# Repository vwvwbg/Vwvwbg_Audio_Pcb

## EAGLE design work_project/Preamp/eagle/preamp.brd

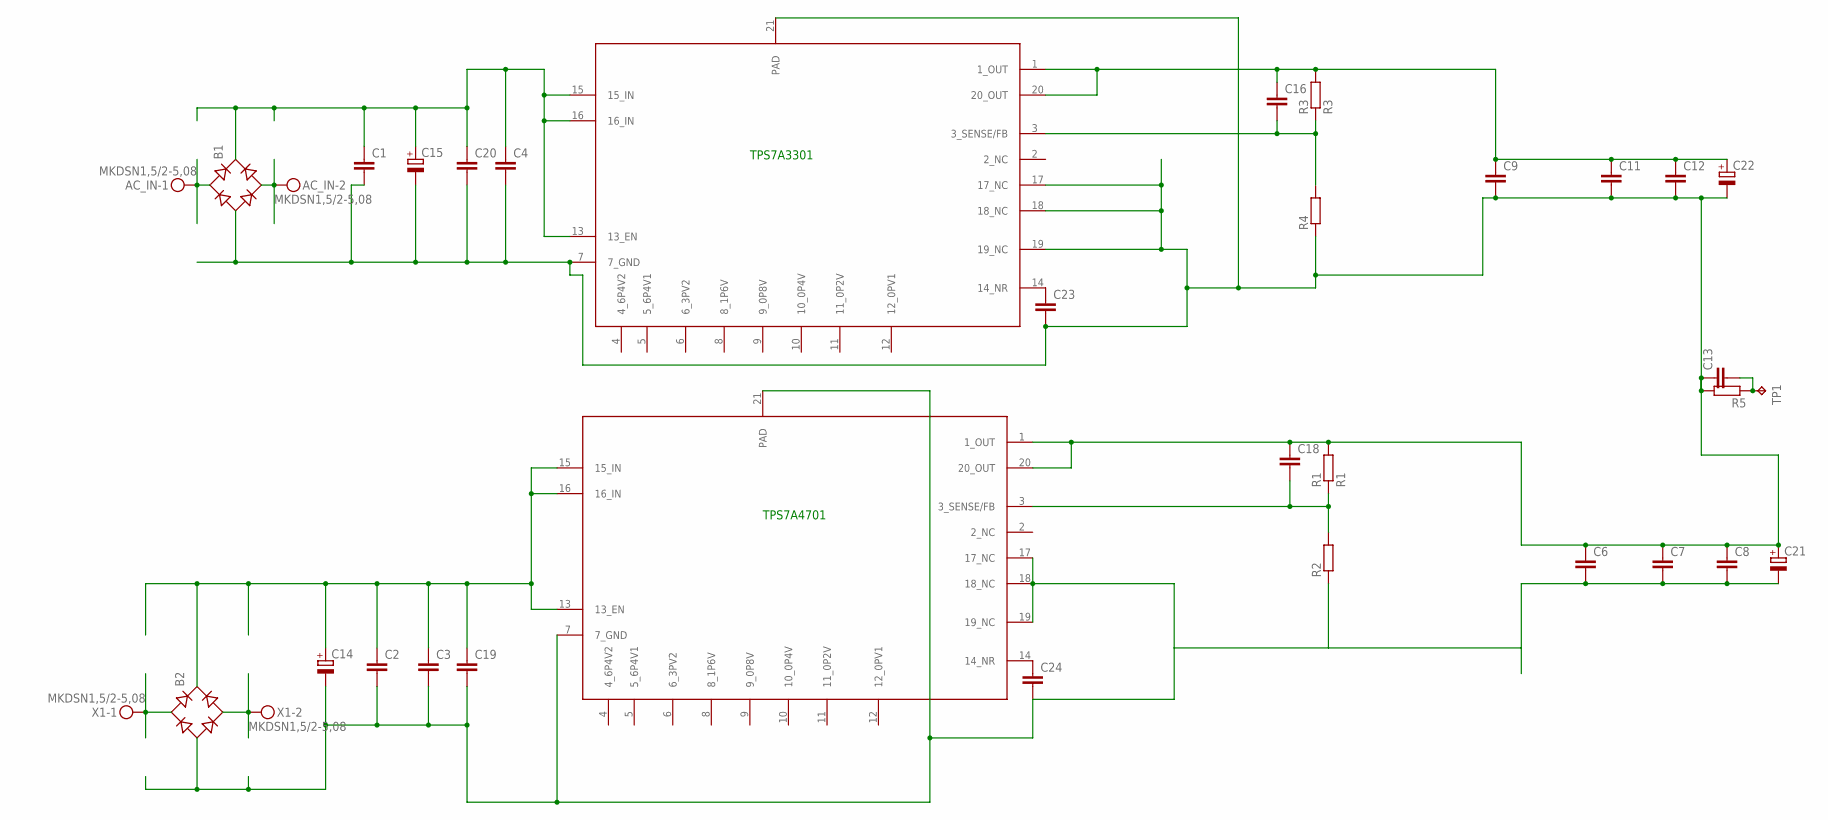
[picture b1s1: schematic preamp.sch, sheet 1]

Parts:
AC_IN: MKDSN1,5/2-5,08
B1, B2: RB1A
C1, C2, C8, C11: C-EUC1210; C1210
C3, C4, C7, C12: C-EUC0805; C0805
C6, C9, C16, C18, C19, C20, C23, C24: C-EUC0603; C0603
C13: C-EU075-042X103; C075-042X103
C14, C15: CPOL-EUE5-13; E5-13
C21, C22: CPOL-EUE3.5-8; E3,5-8
R1: R1; R0805
R2, R4: R-EU_R0805; R0805
R3: R3; R0805
R5: R-EU_0207/12; 0207/12
TP1: TPPAD1-13; P1-13
U$1, U$2: TPS7A4701; QFN65P500X500X100-21N
X1: MKDSN1,5/2-5,08

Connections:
GND: B1.-, C1.2, C4.2, C6.1, C7.1, C8.1, C9.2, C11.2, C12.2, C13.1, C15.-, C18.1, C20.2, C21.+, C22.-, C23.2, R1.2, R4.1, R5.2, U$1.1 (1_OUT), U$1.20 (20_OUT), U$2.7 (7_GND), U$2.17 (17_NC), U$2.18 (18_NC), U$2.19 (19_NC), U$2.21 (PAD); also elsewhere on the board
unnamed: AC_IN.1, B1.AC1
unnamed: B2.+, C2.1, C3.1, C14.+, C19.1, U$1.13 (13_EN), U$1.15 (15_IN), U$1.16 (16_IN)
unnamed: C23.1, U$2.14 (14_NR)
unnamed: C16.2, R3.1, R4.2, U$2.3 (3_SENSE/FB)
unnamed: C24.1, U$1.14 (14_NR)
unnamed: B2.AC2, X1.2
unnamed: B2.AC1, X1.1
unnamed: AC_IN.2, B1.AC2
unnamed: C13.2, R5.1, TP1.TP
unnamed: B1.+, C1.1, C4.1, C15.+, C20.1, U$2.13 (13_EN), U$2.15 (15_IN), U$2.16 (16_IN)
unnamed: C18.2, R1.1, R2.2, U$1.3 (3_SENSE/FB)
V+: C9.1, C11.1, C12.1, C16.1, C22.+, R3.2, U$2.1 (1_OUT), U$2.20 (20_OUT); also elsewhere on the board
V-: B2.-, C2.2, C3.2, C6.2, C7.2, C8.2, C14.-, C19.2, C21.-, C24.2, R2.1, U$1.7 (7_GND), U$1.17 (17_NC), U$1.18 (18_NC), U$1.19 (19_NC), U$1.21 (PAD); also elsewhere on the board

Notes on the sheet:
TPS7A4701
TPS7A3301

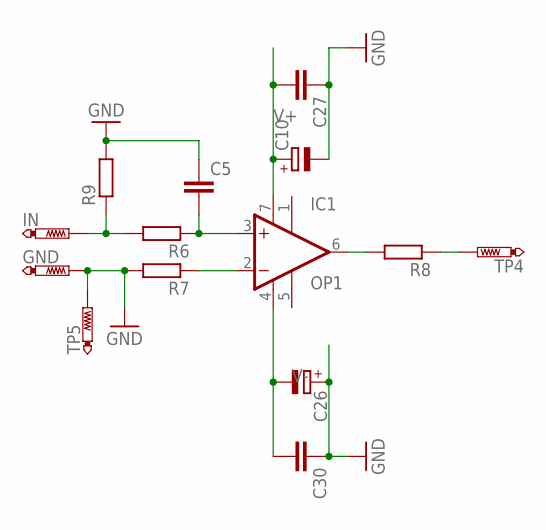
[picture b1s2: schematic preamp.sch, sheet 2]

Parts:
C5: C-EU050-045X075; C050-045X075
C10, C26: CPOL-EUE5-8.5; E5-8,5
C27, C30: C-EU050-030X075; C050-030X075
GND: PTR1PAD1-20; P1-20
IC1: OP1; DIL08
IN: PTR1PAD1-20; P1-20
R6, R7, R8, R9: R-EU_0207/10; 0207/10
TP4, TP5: PTR1PAD1-20; P1-20

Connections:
GND: C5.1, C10.-, C26.+, C27.1, C30.1, GND.TP, R7.2, R9.2, TP5.TP; also elsewhere on the board
unnamed: C5.2, IC1.3 (+IN), R6.1
unnamed: IC1.2 (-IN), R7.1
unnamed: IN.TP, R6.2, R9.1
unnamed: IC1.6 (OUT), R8.2
unnamed: R8.1, TP4.TP
V+: C10.+, C27.2, IC1.7 (V+); also elsewhere on the board
V-: C26.-, C30.2, IC1.4 (V-); also elsewhere on the board

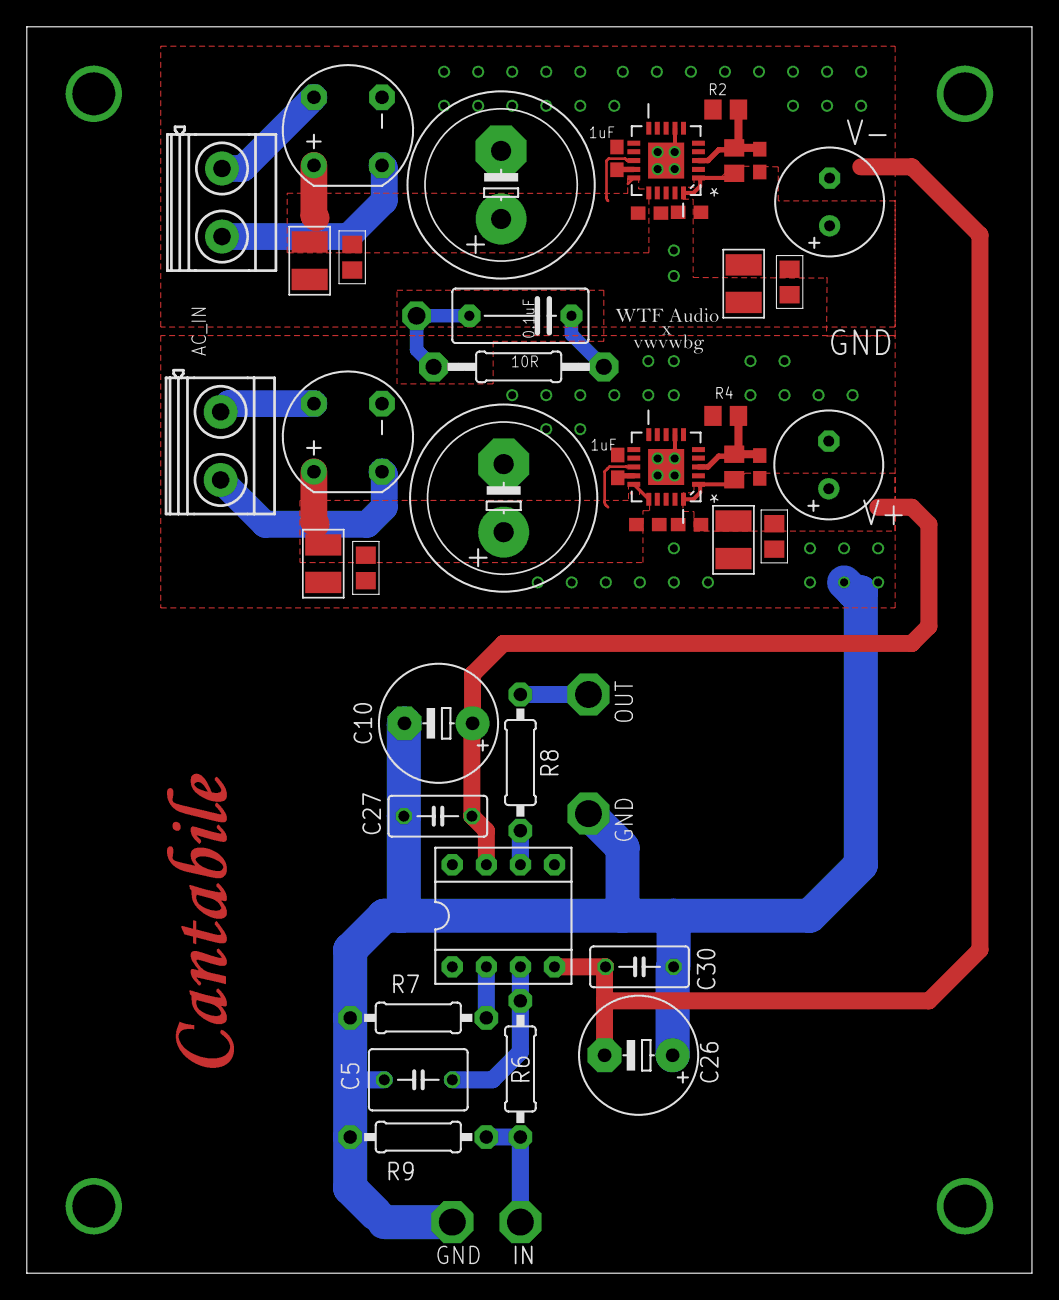
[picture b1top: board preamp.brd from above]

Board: 2 copper layers, 75.0 x 93.0 mm, 47 parts (0 on the bottom side), 19 nets.

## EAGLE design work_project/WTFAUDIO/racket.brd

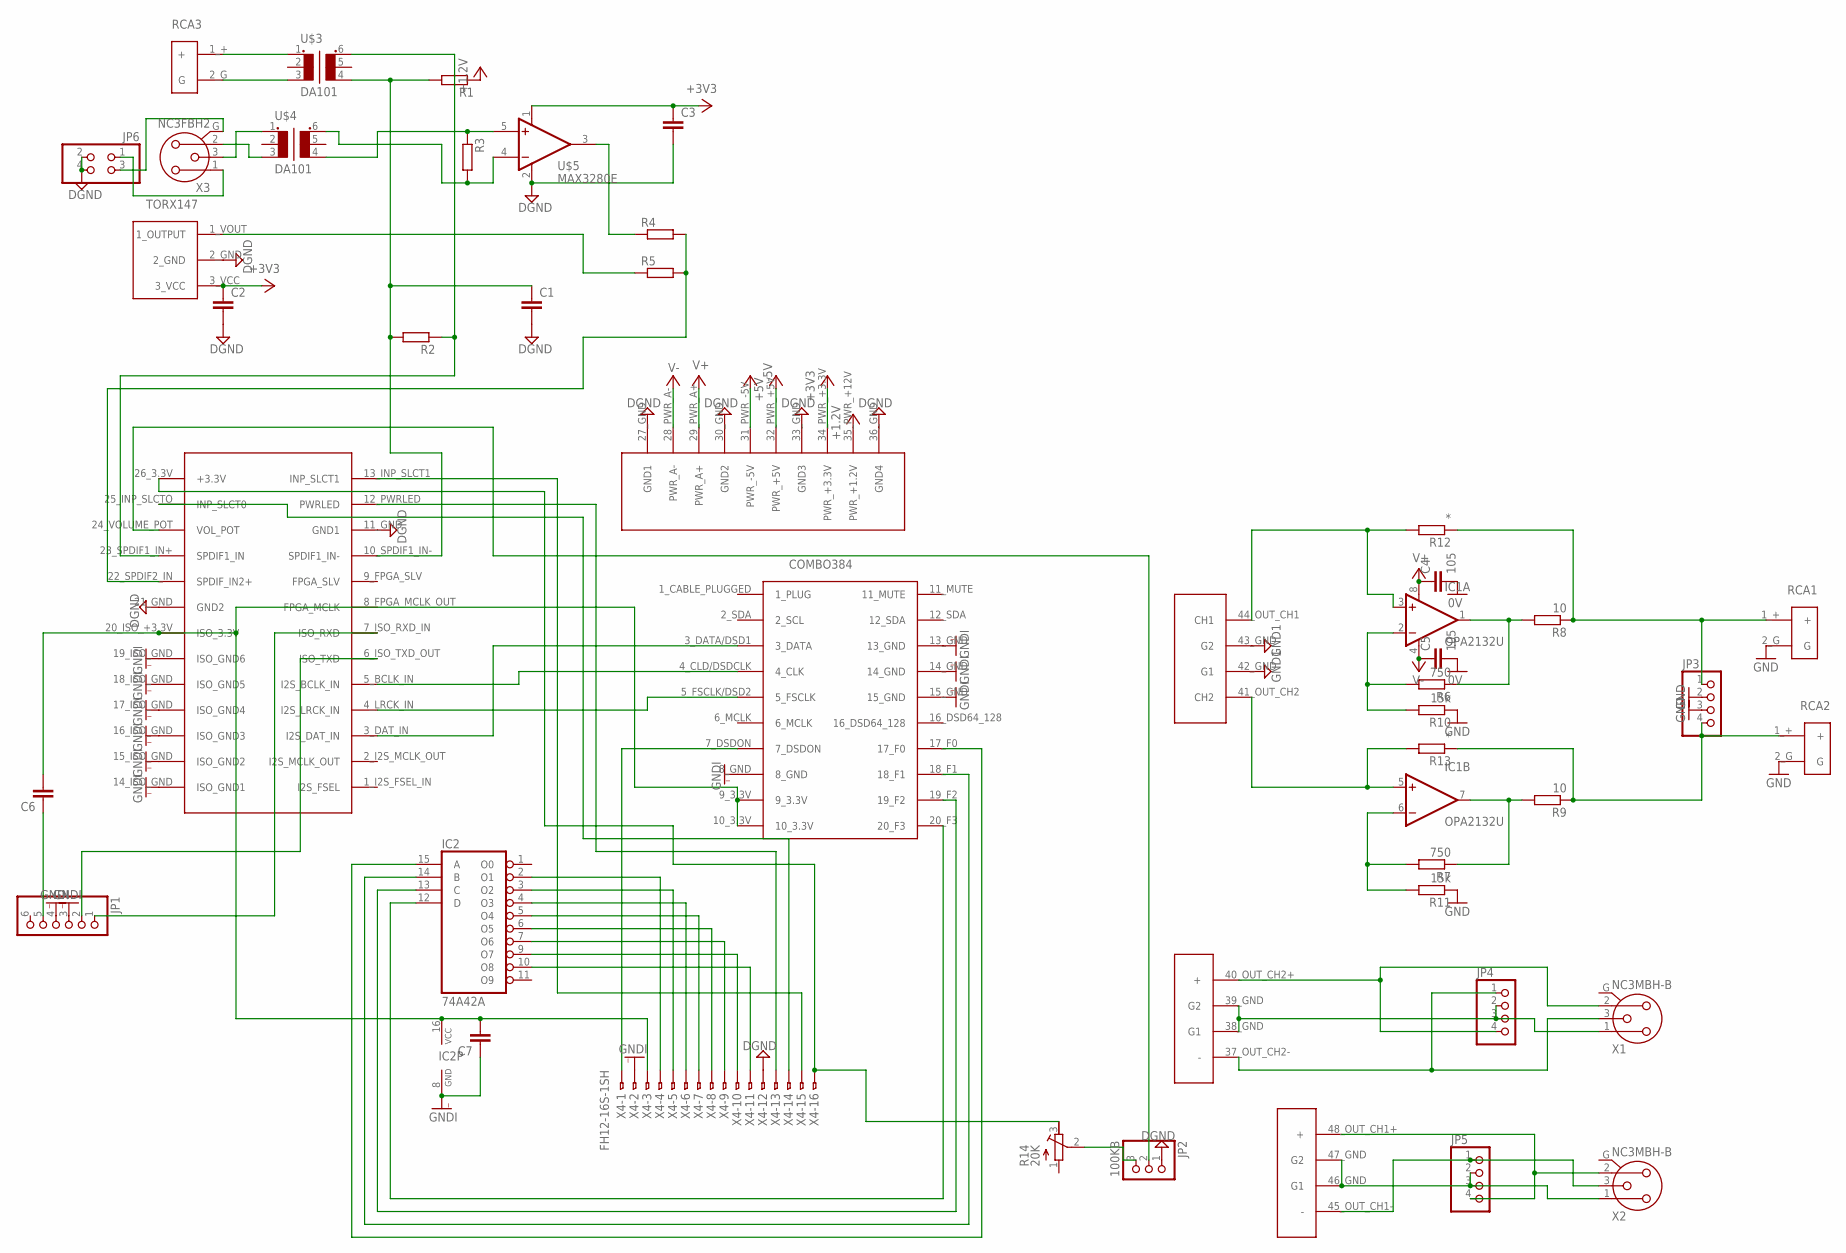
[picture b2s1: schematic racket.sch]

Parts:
C1, C2, C3, C6, C7: C-EUC1206K; C1206K
C4, C5: 105; C1206K
IC1: OPA2132U; SO08
IC2: 74A42A; SO16NS
JP1: PINHD-1X6; 1X06
JP2: 100KB; 1X03
JP3, JP4, JP5: PINHD-1X4; 1X04
JP6: PINHD-2X2; 2X02
R1, R2, R3, R4, R5: R-EU_M1206; M1206
R6, R7: 750; M1206
R8, R9: 10; M1206
R10, R11: 15k; M1206
R12, R13: *; M1206
R14: 20K; RTRIM64W
RCA1, RCA2, RCA3: RCA
U$1: TORX178; TORX178B
U$2: DAM1021
U$3, U$4: DA101; DAC101
U$5: MAX3280E; SOT23-5L
USB1: COMBO384; COMBO384_B
X1, X2: NC3MBH-B
X3: NC3FBH2
X4: FH12-16S-1SH

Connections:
0V: C4.2, C5.2
+1V2: R1.1, U$2.35_PWR_+12V (PWR_+1.2V)
+3V3: C2.1, C3.1, U$1.3_VCC, U$2.34_PWR_+3.3V (PWR_+3.3V), U$5.1 (V+)
+5V: U$2.32_PWR_+5V (PWR_+5V)
-5V: U$2.31_PWR_-5V (PWR_-5V)
DGND: C1.2, C2.2, C3.2, JP2.1, JP6.2, JP6.4, U$1.2_GND, U$2.11_GND (GND1), U$2.21_GND (GND2), U$2.27_GND (GND1), U$2.30_GND (GND2), U$2.33_GND (GND3), U$2.36_GND (GND4), U$5.2 (V-), X4.12
GND: JP3.2, JP3.3, R10.1, R11.1, RCA1.2_G (G), RCA2.2_G (G)
GND1: U$2.42_GND (G1), U$2.43_GND (G2)
GNDI: C7.1, IC2.8 (GND), JP1.3, JP1.4, U$2.14_ISO_GND (ISO_GND1), U$2.15_ISO_GND (ISO_GND2), U$2.16_ISO_GND (ISO_GND3), U$2.17_ISO_GND (ISO_GND4), U$2.18_ISO_GND (ISO_GND5), U$2.19_ISO_GND (ISO_GND6), USB1.8_GND, USB1.13_GND, USB1.14_GND, USB1.15_GND, X4.2
unnamed: RCA3.1_+ (+), U$3.1
unnamed: RCA3.2_G (G), U$3.3
unnamed: JP3.4, R9.1, R13.1, RCA2.1_+ (+)
unnamed: C1.1, R1.2, R2.2, U$2.10_SPDIF1_IN- (SPDIF1_IN-), U$3.4 (6)
unnamed: R2.1, U$2.23_SPDIF1_IN+ (SPDIF1_IN), U$3.6 (4)
unnamed: JP3.1, R8.1, R12.1, RCA1.1_+ (+)
unnamed: U$4.3, X3.2
unnamed: U$4.1, X3.3
unnamed: R3.1, U$4.4 (6), U$5.5 (+IN)
unnamed: R3.2, U$4.6 (4), U$5.4 (-IN)
unnamed: R4.1, U$5.3 (OUT)
unnamed: R5.1, U$1.1_VOUT (1_OUTPUT)
unnamed: R4.2, R5.2, U$2.22_SPDIF2_IN (SPDIF_IN2+)
unnamed: IC1.3 (+IN), R12.2, U$2.44_OUT_CH1 (CH1)
unnamed: JP1.2, U$2.6_ISO_TXD_OUT (ISO_TXD)
unnamed: IC1.2 (-IN), R6.2, R10.2
unnamed: IC1.1 (OUT), R6.1, R8.2
unnamed: IC1.6 (-IN), R7.2, R11.2
unnamed: IC1.7 (OUT), R7.1, R9.2
unnamed: IC1.5 (+IN), R13.2, U$2.41_OUT_CH2 (CH2)
unnamed: JP1.1, U$2.7_ISO_RXD_IN (ISO_RXD)
unnamed: C6.2, C7.2, IC2.16 (VCC), U$2.20_ISO_+3.3V (ISO_3.3V), USB1.9_3.3V, USB1.10_3.3V, X4.3
unnamed: C6.1, JP1.5
unnamed: IC2.4 (O3), X4.6
unnamed: USB1.7_DSDON, X4.1
unnamed: IC2.5 (O4), X4.7
unnamed: IC2.2 (O1), X4.4
unnamed: IC2.3 (O2), X4.5
unnamed: IC2.6 (O5), X4.8
unnamed: IC2.7 (O6), X4.9
unnamed: IC2.9 (O7), X4.10
unnamed: IC2.10 (O8), X4.11
unnamed: U$2.12_PWRLED (PWRLED), X4.13
unnamed: U$2.25_INP_SLCTO (INP_SLCT0), X4.14
unnamed: R14.3 (E), U$2.26_3.3V (+3.3V), X4.16
unnamed: U$2.13_INP_SLCT1 (INP_SLCT1), X4.15
unnamed: IC2.12 (D), USB1.20_F3
unnamed: IC2.13 (C), USB1.19_F2
unnamed: IC2.14 (B), USB1.18_F1
unnamed: IC2.15 (A), USB1.17_F0
unnamed: JP2.2, U$2.24_VOLUME_POT (VOL_POT)
unnamed: JP2.3, R14.2 (S)
unnamed: U$2.3_DAT_IN (I2S_DAT_IN), USB1.3_DATA/DSD1 (3_DATA)
unnamed: U$2.4_LRCK_IN (I2S_LRCK_IN), USB1.5_FSCLK/DSD2 (5_FSCLK)
unnamed: U$2.5_BCLK_IN (I2S_BCLK_IN), USB1.4_CLD/DSDCLK (4_CLK)
unnamed: JP4.4, U$2.40_OUT_CH2+ (+), X1.2
unnamed: JP4.1, U$2.37_OUT_CH2- (-), X1.3
unnamed: JP4.2, JP4.3, U$2.38_GND (G1), U$2.39_GND (G2), X1.1
unnamed: JP5.2, JP5.3, U$2.46_GND (G1), U$2.47_GND (G2), X2.1
unnamed: JP5.4, U$2.48_OUT_CH1+ (+), X2.2
unnamed: JP6.3, X3.G
unnamed: JP5.1, U$2.45_OUT_CH1- (-), X2.3
unnamed: JP6.1, X3.1
V+: C4.1, IC1.8 (V+), U$2.29_PWR_A+ (PWR_A+)
V-: C5.1, IC1.4 (V-), U$2.28_PWR_A- (PWR_A-)

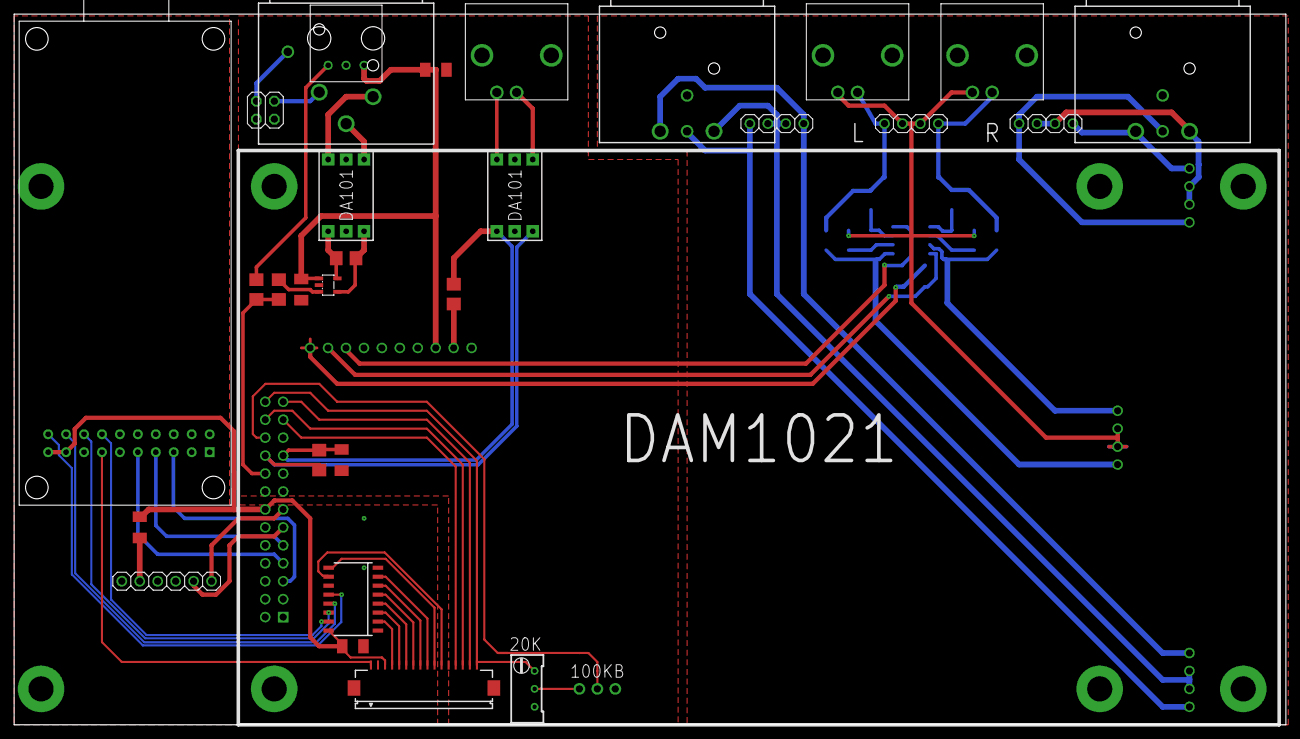
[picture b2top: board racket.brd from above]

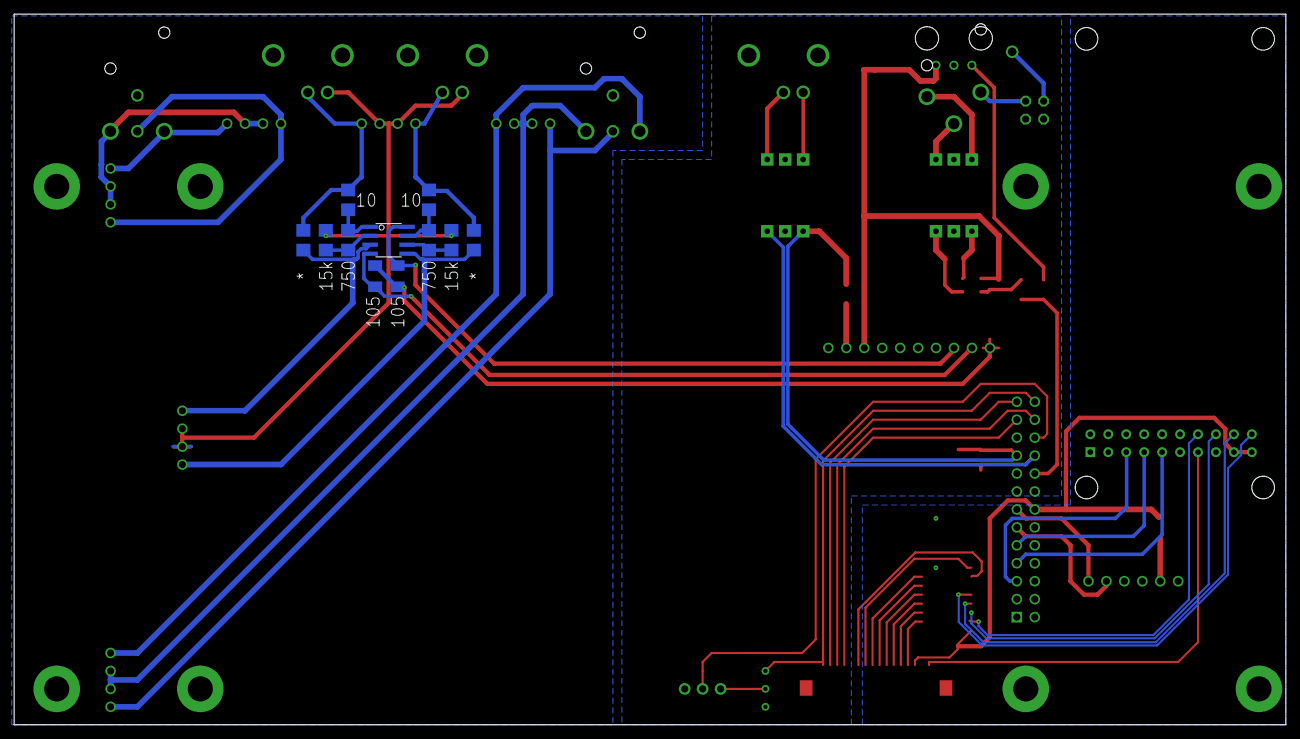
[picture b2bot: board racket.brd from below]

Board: 2 copper layers, 180.0 x 100.6 mm, 42 parts (11 on the bottom side), 62 nets.

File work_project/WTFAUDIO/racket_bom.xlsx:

Part | Value | Device | Package | Description
C1 |  | C-EUC1206K | C1206K | CAPACITOR, European symbol
C2 |  | C-EUC1206K | C1206K | CAPACITOR, European symbol
C3 |  | C-EUC1206K | C1206K | CAPACITOR, European symbol
C4 | 105 | C-EUC1206K | C1206K | CAPACITOR, European symbol
C5 | 105 | C-EUC1206K | C1206K | CAPACITOR, European symbol
C6 |  | C-EUC1206K | C1206K | CAPACITOR, European symbol
C7 |  | C-EUC1206K | C1206K | CAPACITOR, European symbol
IC1 | OPA2132U | OPA2132U | SO08 | High Speed FET-Input Operational Amplifiers<
IC2 | 74A42A | 74A42A | SO16NS | 4-line to 10-line DECODER (1-of-10)
JP1 |  | PINHD-1X6 | 1X06 | PIN HEADER
JP2 | 100KB | PINHD-1X3 | 1X03 | PIN HEADER
JP3 |  | PINHD-1X4 | 1X04 | PIN HEADER
JP4 |  | PINHD-1X4 | 1X04 | PIN HEADER
JP5 |  | PINHD-1X4 | 1X04 | PIN HEADER
JP6 |  | PINHD-2X2 | 2X02 | PIN HEADER
R1 |  | R-EU_M1206 | M1206 | RESISTOR, European symbol
R2 |  | R-EU_M1206 | M1206 | RESISTOR, European symbol
R3 |  | R-EU_M1206 | M1206 | RESISTOR, European symbol
R4 |  | R-EU_M1206 | M1206 | RESISTOR, European symbol
R5 |  | R-EU_M1206 | M1206 | RESISTOR, European symbol
R6 | 750 | R-EU_M1206 | M1206 | RESISTOR, European symbol
R7 | 750 | R-EU_M1206 | M1206 | RESISTOR, European symbol
R8 | 10 | R-EU_M1206 | M1206 | RESISTOR, European symbol
R9 | 10 | R-EU_M1206 | M1206 | RESISTOR, European symbol
R10 | 15k | R-EU_M1206 | M1206 | RESISTOR, European symbol
R11 | 15k | R-EU_M1206 | M1206 | RESISTOR, European symbol
R12 | * | R-EU_M1206 | M1206 | RESISTOR, European symbol
R13 | * | R-EU_M1206 | M1206 | RESISTOR, European symbol
R14 | 20K | R-TRIMM64W | RTRIM64W | Trimm resistor
RCA1 | RCA | RCA | RCA
RCA2 | RCA | RCA | RCA
RCA3 | RCA | RCA | RCA
U$1 | TORX178 | TORX178 | TORX178B
U$2 | DAM1021 | DAM1021 | DAM1021
U$3 | DA101 | DA101 | DAC101
U$4 | DA101 | DA101 | DAC101
U$5 | MAX3280E | MAX3280E | SOT23-5L
USB1 | COMBO384 | COMBO384 | COMBO384_B
X1 | NC3MBH-B | NC3MBH-B | NC3MBH-B | Neutrik Audio Connector XLR SERIES
X2 | NC3MBH-B | NC3MBH-B | NC3MBH-B | Neutrik Audio Connector XLR SERIES
X3 | NC3FBH2 | NC3FBH2 | NC3FBH2 | Neutrik Audio Connector XLR SERIES
X4 | FH12-16S-1SH | FH12-16S-1SH | FH12-16S-1SH | 1mm Pitch Connectors For FPC/FFC

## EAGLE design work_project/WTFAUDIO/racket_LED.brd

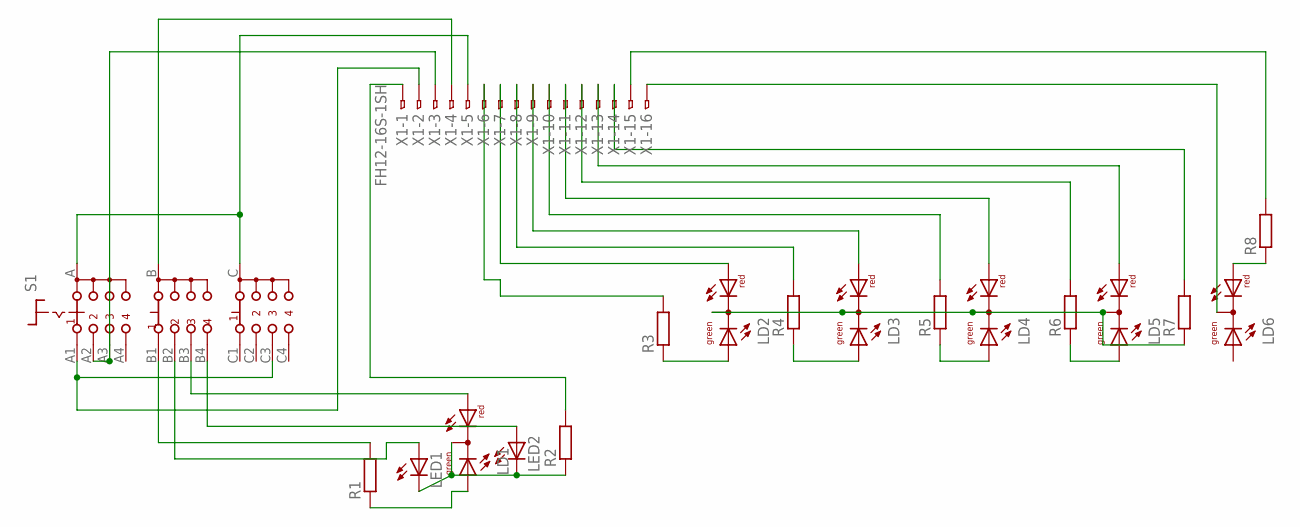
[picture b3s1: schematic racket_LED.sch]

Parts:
LD1, LD2, LD3, LD4, LD5, LD6: DUOLED-RG-C; DUOLED-C-5MM
LED1, LED2: LED3MM
R1, R2, R3, R4, R5, R6, R7, R8: R-EU_M1206; M1206
S1: CK103X04
X1: FH12-16S-1SH

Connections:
unnamed: S1.B, X1.4
unnamed: S1.A1, S1.C3, X1.2
unnamed: S1.A, S1.C, X1.5
unnamed: R1.2, S1.B1
unnamed: LD1.AX (AG), R1.1
unnamed: LD1.C, LED1.K (C), LED2.K (C), R2.1
unnamed: R2.2, X1.1
unnamed: LED2.A, S1.B4
unnamed: LD1.AR, S1.B3
unnamed: LED1.A, S1.B2
unnamed: S1.A2, S1.A3, X1.3
unnamed: LD2.AX (AG), R3.1
unnamed: R3.2, X1.6
unnamed: LD2.AR, X1.7
unnamed: LD3.AX (AG), R4.1
unnamed: LD4.AX (AG), R5.1
unnamed: R4.2, X1.8
unnamed: LD3.AR, X1.9
unnamed: R5.2, X1.10
unnamed: LD4.AR, X1.11
unnamed: LD5.AX (AG), R6.1
unnamed: R6.2, X1.12
unnamed: LD5.AR, X1.13
unnamed: LD2.C, LD3.C, LD4.C, LD5.C, R7.1
unnamed: R7.2, X1.14
unnamed: LD6.C, X1.16
unnamed: R8.2, X1.15
unnamed: LD6.AR, R8.1

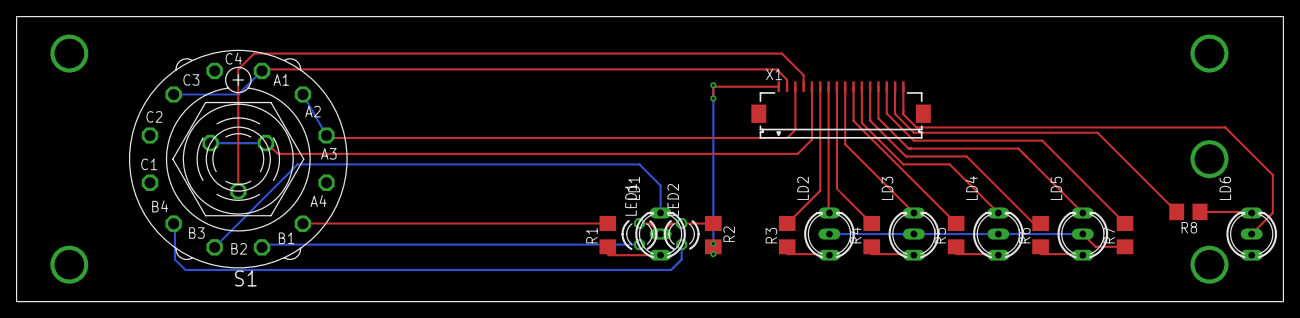
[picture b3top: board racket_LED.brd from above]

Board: 2 copper layers, 152.4 x 34.3 mm, 18 parts (0 on the bottom side), 28 nets.

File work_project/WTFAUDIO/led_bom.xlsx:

Part | Value | Device | Package | Description
LD1 |  | DUOLED-RG-C | DUOLED-C-5MM | DUO LED
LD2 |  | DUOLED-RG-C | DUOLED-C-5MM | DUO LED
LD3 |  | DUOLED-RG-C | DUOLED-C-5MM | DUO LED
LD4 |  | DUOLED-RG-C | DUOLED-C-5MM | DUO LED
LD5 |  | DUOLED-RG-C | DUOLED-C-5MM | DUO LED
LD6 |  | DUOLED-RG-C | DUOLED-C-5MM | DUO LED
LED1 |  | LED3MM | LED3MM | LED
LED2 |  | LED3MM | LED3MM | LED
R1 |  | R-EU_M1206 | M1206 | RESISTOR, European symbol
R2 |  | R-EU_M1206 | M1206 | RESISTOR, European symbol
R3 |  | R-EU_M1206 | M1206 | RESISTOR, European symbol
R4 |  | R-EU_M1206 | M1206 | RESISTOR, European symbol
R5 |  | R-EU_M1206 | M1206 | RESISTOR, European symbol
R6 |  | R-EU_M1206 | M1206 | RESISTOR, European symbol
R7 |  | R-EU_M1206 | M1206 | RESISTOR, European symbol
R8 |  | R-EU_M1206 | M1206 | RESISTOR, European symbol
S1 |  | CK103X04 | CK103X04 | ROTARY SWITCH
X1 | FH12-16S-1SH | FH12-16S-1SH | FH12-16S-1SH | 1mm Pitch Connectors For FPC/FFC
